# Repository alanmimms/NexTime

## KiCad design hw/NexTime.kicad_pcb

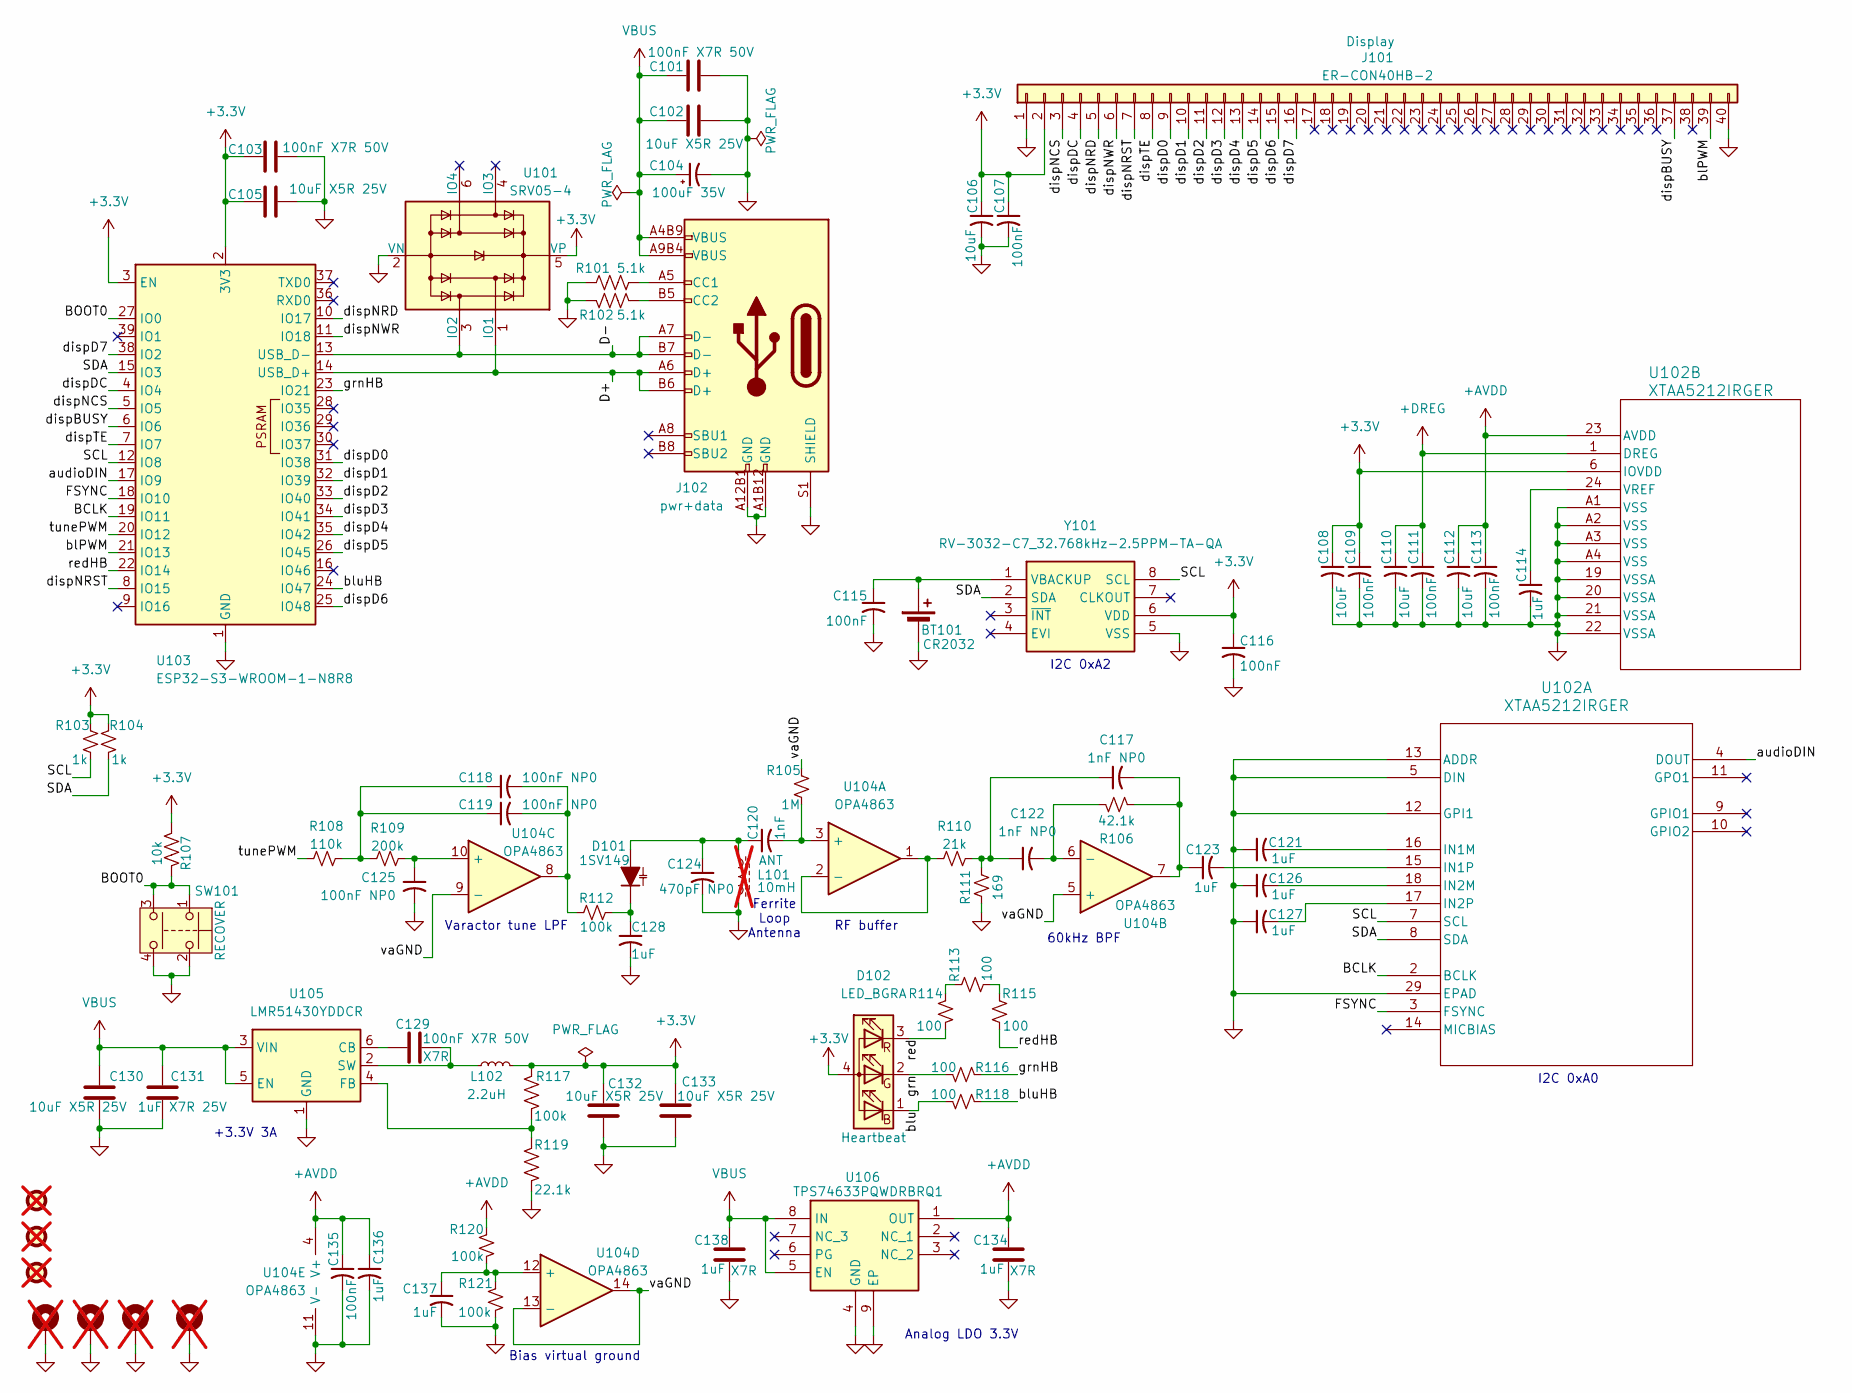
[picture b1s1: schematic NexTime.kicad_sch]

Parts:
BT101: CR2032; BatteryHolder_Keystone_3034_1x20mm
C101, C103: 100nF X7R 50V; C_0603_1608Metric; MPN KGM15BR71H104KT; LCSC C24452
C102, C105: 10uF X5R 25V; C_0603_1608Metric; MPN CM105X5R106M25AT; LCSC C96446
C104: 100uF 35V; C_Elec_8x6.2; MPN MAL214297007E3; LCSC C1849748
C106, C108, C110, C112: 10uF; C_0402_1005Metric
C107, C109, C111, C113, C115, C116, C135: 100nF; C_0402_1005Metric
C114, C121, C123, C126, C127, C128, C136, C137: 1uF; C_0402_1005Metric; MPN GRM155Z71A105KE1D; Mouser_PN 81-GRM155Z71A105KE1D
C117, C122: 1nF NP0; C_0402_1005Metric
C118, C119, C125: 100nF NP0; C_1206_3216Metric
C120: 1nF; C_0402_1005Metric
C124: 470pF NP0; C_0402_1005Metric
C129: 100nF X7R 50V; C_0603_1608Metric; MPN KGM15BR71H104KT; LCSC_PN C24452
C130: 10uF X5R 25V; C_0603_1608Metric; MPN CM105X5R106M25AT; LCSC_PN C327087
C131: 1uF X7R 25V; C_0603_1608Metric; MPN CM105X7R105K25AT; LCSC_PN C301928
C132, C133: 10uF X5R 25V; C_0603_1608Metric; Manufacturer_Part_Number 81-GXT155R71E223KE1D; Mouser Part Number 963-MLAST168BB5106MT
C134, C138: 1uF; C_0402_1005Metric; MPN GRM155Z71A105KE1D; LCSC_PN C301928
D101: 1SV149; Heraeus_TO-92-2
D102: LED_BGRA; UHD111AFKAC3K23E1L3VG5ZB3Z3; MPN UHD111A-FKA-C3K23E1L3VG5ZB3Z3; Mouser_PN 941-UHD1AA3K3E3V53Z3
FID101, FID102, FID103: Fiducial; Fiducial_1mm_Mask2mm; LCSC DNP; not fitted
H101, H102, H103, H104: MountingHole_Pad; MountingHole_3.2mm_M3_ISO7380_Pad; LCSC DNP; not fitted
J101: ER-CON40HB-2
J102: pwr+data; USB_C_Receptacle_HRO_TYPE-C-31-M-12-bursted; MPN TYPE-C-31-M-12; LCSC_PN C165948
L101: 10mH; PinHeader_1x02_P1.27mm_Vertical_SMD_Pin1Left; not fitted
L102: 2.2uH; L_1008_2520Metric; MPN AIML-1008HC-2R2M-T; LCSC_PN C86089
R101, R102: 5.1k; R_0402_1005Metric; MPN MCS04020C5101FE000; LCSC_PN C854378
R103, R104: 1k; R_0402_1005Metric
R105: 1M; R_0402_1005Metric
R106: 42.1k; R_0402_1005Metric
R107: 10k; R_0402_1005Metric; LCSC_PN C723366
R108: 110k; R_0402_1005Metric
R109: 200k; R_0402_1005Metric
R110: 21k; R_0402_1005Metric
R111: 169; R_0402_1005Metric
R112, R120, R121: 100k; R_0402_1005Metric; MPN CRT0402-FZ-1003GLF; Mouser_PN 652-CRT0402FZ1003GLF
R113, R114, R115, R116, R118: 100; R_0402_1005Metric
R117: 100k; R_0402_1005Metric; MPN CRT0402-FZ-1003GLF; LCSC_PN C728576
R119: 22.1k; R_0402_1005Metric; MPN RT0402FRD0722K1L; LCSC_PN C284424
SW101: Push button switch; EVQPUC02K
U101: SRV05-4; SOT-23-6; MPN SRV05-4.TCT; LCSC C2836319
U102: XTAA5212IRGER; TAA5212
U103: ESP32-S3-WROOM-1-N8R8; ESP32-S3-WROOM-1; Mouser Part Number ESP32-S3-WROOM-1-N8R8; LCSC C2913204
U104: OPA4863; TSSOP-14_4.4x5mm_P0.65mm
U105: LMR51430YDDCR; SOT-23-6; MPN LMR51430YDDCR; LCSC_PN C5185863
U106: TPS74633PQWDRBRQ1; SON65P300X300X100-9N-D; MPN TPS74633PQWDRBRQ1; Mouser_PN 595-PS74633PQWDRBRQ1
Y101: RV-3032-C7_32.768kHz-2.5PPM-TA-QA; RV3032C7; Mouser Part Number 428-203853-MG01

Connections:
+3.3V: C103.1, C105.1, C106.1, C107.1, C108.1, C109.1, C116.1, C132.1, C133.1, D102.4 (A), J101.2, L102.2, R103.2, R104.2, R107.1, R117.2, U101.5 (VP), U102.6 (IOVDD), U103.2 (3V3), U103.3 (EN), Y101.6 (VDD)
+AVDD: C112.1, C113.1, C134.1, C135.1, C136.1, R120.2, U102.23 (AVDD), U104.4 (V+), U106.1 (OUT)
+DREG: C110.1, C111.1, U102.1 (DREG)
/BCLK: U102.2 (BCLK), U103.19 (IO11)
/BOOT0: R107.2, SW101.1, SW101.3, U103.27 (IO0)
/D+: J102.A6 (D+), J102.B6 (D+), U101.1 (IO1), U103.14 (USB_D+)
/D-: J102.A7 (D-), J102.B7 (D-), U101.3 (IO2), U103.13 (USB_D-)
/FSYNC: U102.3 (FSYNC), U103.18 (IO10)
/SCL: R103.1, U102.7 (SCL), U103.12 (IO8), Y101.8 (SCL)
/SDA: R104.1, U102.8 (SDA), U103.15 (IO3), Y101.2 (SDA)
/audioDIN: U102.4 (DOUT), U103.17 (IO9)
/blPWM: J101.39, U103.21 (IO13)
/blu: D102.1 (BK), R118.2
/bluHB: R118.1, U103.24 (IO47)
/dispBUSY: J101.37, U103.6 (IO6)
/dispD0: J101.9, U103.31 (IO38)
/dispD1: J101.10, U103.32 (IO39)
/dispD2: J101.11, U103.33 (IO40)
/dispD3: J101.12, U103.34 (IO41)
/dispD4: J101.13, U103.35 (IO42)
/dispD5: J101.14, U103.26 (IO45)
/dispD6: J101.15, U103.25 (IO48)
/dispD7: J101.16, U103.38 (IO2)
/dispDC: J101.4, U103.4 (IO4)
/dispNCS: J101.3, U103.5 (IO5)
/dispNRD: J101.5, U103.10 (IO17)
/dispNRST: J101.7, U103.8 (IO15)
/dispNWR: J101.6, U103.11 (IO18)
/dispTE: J101.8, U103.7 (IO7)
/grn: D102.2 (GK), R116.2
/grnHB: R116.1, U103.23 (IO21)
/red: D102.3 (RK), R114.2
/redHB: R115.2, U103.22 (IO14)
/tunePWM: R108.1, U103.20 (IO12)
/vaGND: R105.2, U104.5 (+), U104.9 (-), U104.13 (-), U104.14
GND: BT101.2 (-), C101.2, C102.2, C103.2, C104.2, C105.2, C106.2, C107.2, C108.2, C109.2, C110.2, C111.2, C112.2, C113.2, C114.2, C115.2, C116.2, C121.1, C124.2, C125.2, C126.1, C127.1, C128.2, C130.2, C131.2, C132.2, C133.2, C134.2, C135.2, C136.2, C137.2, C138.2, H101.1, H102.1, H103.1, H104.1, J101.1, J101.40, J102.A1B12 (GND), J102.A12B1 (GND), J102.S1 (SHIELD), L101.2, R101.2, R102.2, R111.1, R119.1, R121.1, SW101.2, SW101.4, U101.2 (VN), U102.5 (DIN), U102.12 (GPI1), U102.13 (ADDR), U102.19 (VSSA), U102.20 (VSSA), U102.21 (VSSA), U102.22 (VSSA), U102.29 (EPAD), U102.A1 (VSS), U102.A2 (VSS), U102.A3 (VSS), U102.A4 (VSS), U103.1 (GND), U103.40 (GND), U103.41 (GND), U104.11 (V-), U105.1 (GND), U106.4 (GND), U106.9 (EP), Y101.5 (VSS)
unnamed: BT101.1 (+), C115.1, Y101.1 (VBACKUP)
unnamed: C117.1, C122.1, R110.2, R111.2
unnamed: C117.2, C123.1, R106.2, U104.7
unnamed: C118.1, C119.1, R108.2, R109.1
unnamed: C118.2, C119.2, R112.1, U104.8
unnamed: C120.1, C124.1, D101.2 (A), L101.1
unnamed: C128.1, D101.1 (K), R112.2
unnamed: J102.A5 (CC1), R101.1
unnamed: J102.B5 (CC2), R102.1
unnamed: R113.1, R114.1
unnamed: R113.2, R115.1
unnamed: C121.2, U102.16 (IN1M)
unnamed: C123.2, U102.15 (IN1P)
unnamed: C126.2, U102.18 (IN2M)
unnamed: C127.2, U102.17 (IN2P)
unnamed: C114.1, U102.24 (VREF)
unnamed: C120.2, R105.1, U104.3 (+)
unnamed: R110.1, U104.1, U104.2 (-)
unnamed: C122.2, R106.1, U104.6 (-)
unnamed: C125.1, R109.2, U104.10 (+)
unnamed: C137.1, R120.1, R121.2, U104.12 (+)
unnamed: C129.1, U105.6 (CB)
unnamed: R117.1, R119.2, U105.4 (FB)
unnamed: C129.2, L102.1, U105.2 (SW)
VBUS: C101.1, C102.1, C104.1, C130.1, C131.1, C138.1, J102.A4B9 (VBUS), J102.A9B4 (VBUS), U105.3 (VIN), U105.5 (EN), U106.5 (EN), U106.8 (IN)

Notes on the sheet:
I2C 0xA2
Bias virtual ground
I2C 0xA0
Analog LDO 3.3V
RF buffer
Varactor tune LPF
60kHz BPF
Ferrite Loop Antenna
+3.3V 3A

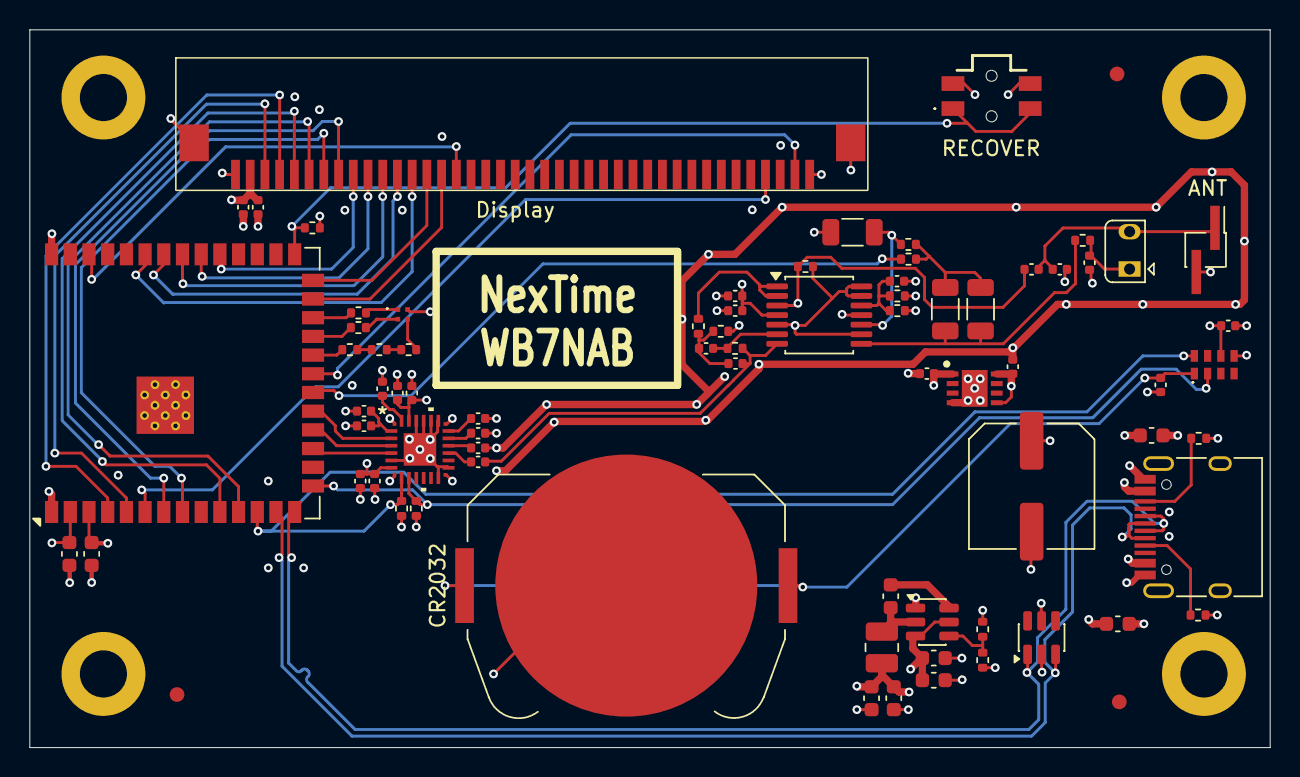
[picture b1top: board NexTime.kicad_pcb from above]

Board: 4 copper layers, 84.2 x 48.8 mm, 81 parts (0 on the bottom side), 61 nets.

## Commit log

2026-06-02 Schematic "done" and passing ERC. Layout also.
2026-06-02 Added RECOVER pushbutton. Cleared the way for display but not added yet.
2026-06-03 Update 3d models for parts. Display conn still missing
2026-06-03 Finally have 3d for display connector (mostly ok)
2026-06-03 Improve connector 3d model and footprint now matches connector drawing
2026-06-03 Improve power routing
2026-06-03 Ignore my 3d export
2026-06-03 Move things around to make room for FLAT CR2032 bat holder. Add RF shield ring around high Z sensitivity circuitry. Shove display connector toward board left and move RECOVER button up on top by disp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
